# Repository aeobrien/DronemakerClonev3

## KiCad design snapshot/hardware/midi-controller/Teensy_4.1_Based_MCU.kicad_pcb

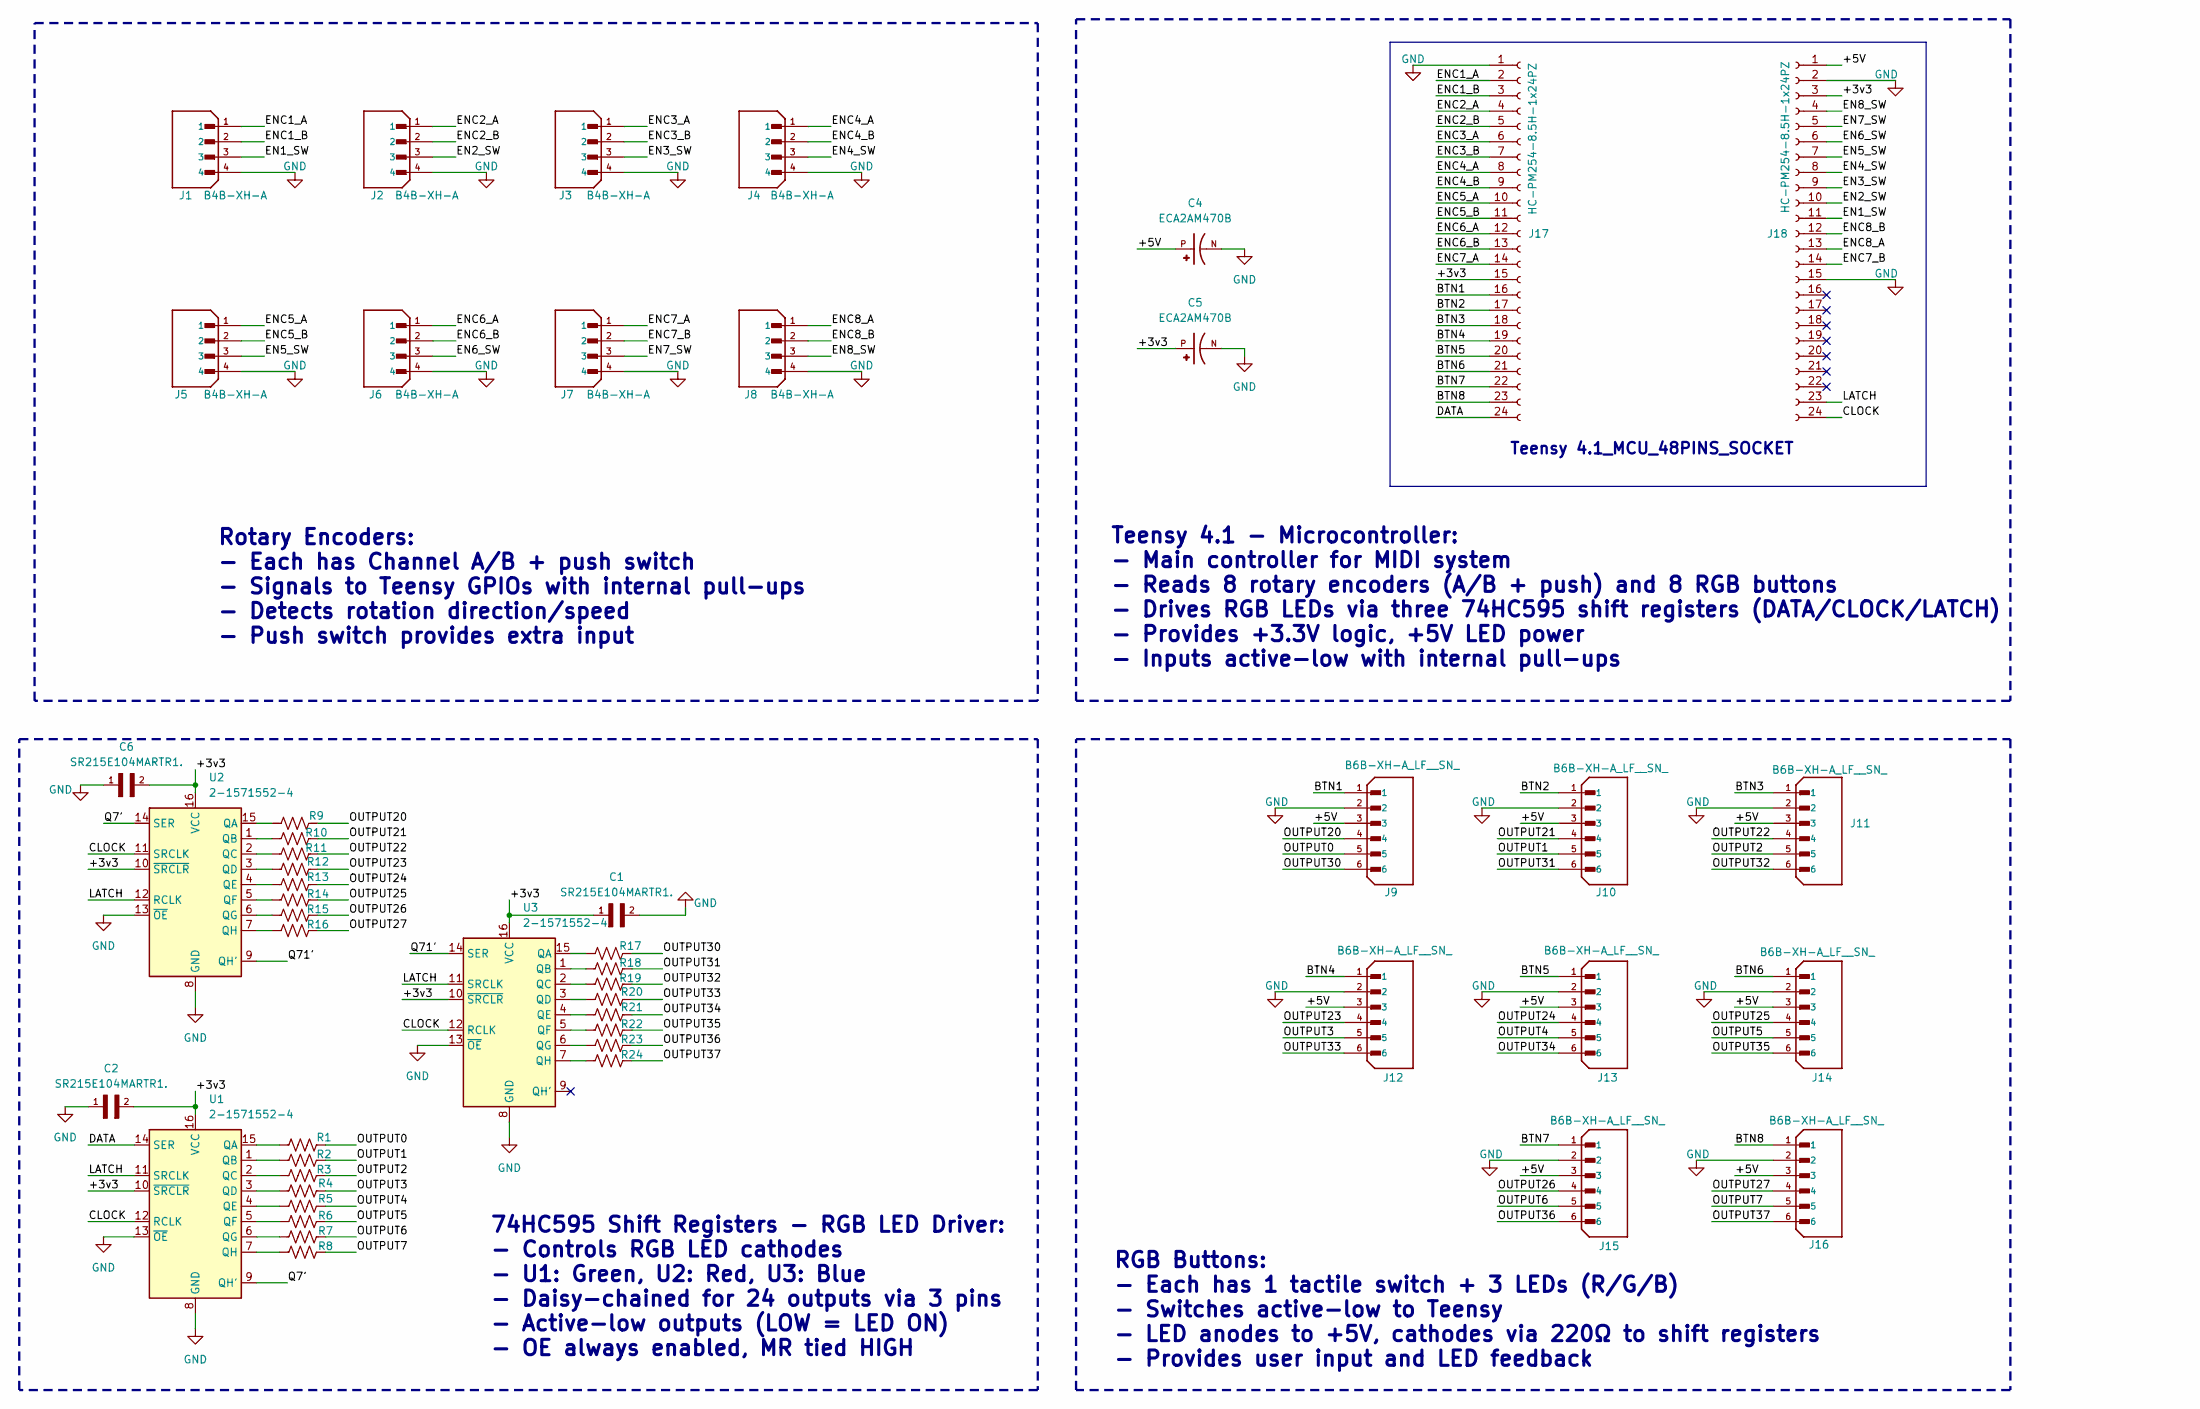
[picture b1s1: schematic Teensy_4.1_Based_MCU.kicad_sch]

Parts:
C1, C2, C6: SR215E104MARTR1.; CAPRR508W50L508T317H508; PARTREV 081816
C4, C5: ECA2AM470B; CAPPRD500W60D1000H2000; PARTREV 20-DEC-19
J1, J2, J3, J4, J5, J6, J7, J8: B4B-XH-A; JST_B4B-XH-A; PARTREV 7/4/21
J9, J10, J11, J12, J13, J14, J15, J16: B6B-XH-A_LF__SN_; JST_B6B-XH-A; PARTREV 7/4/21
J17, J18: HC-PM254-8.5H-1x24PZ; PinSocket_1x24_P2.54mm_Vertical
R1, R2, R3, R4, R5, R6, R7, R8, R9, R10, R11, R12, R13, R14, R15, R16, R17, R18, R19, R20, R21, R22, R23, R24: 220R; R_Axial_DIN0207_L6.3mm_D2.5mm_P10.16mm_Horizontal
U1, U2, U3: 2-1571552-4; DIP-16_W7.62mm_Socket

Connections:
/+3v3: C1.1, C2.2, C5.P, C6.2, J17.15, J18.3, U1.10 (~SRCLR), U1.16 (VCC), U2.10 (~SRCLR), U2.16 (VCC), U3.10 (~SRCLR), U3.16 (VCC)
/+5V: C4.P, J9.3, J10.3, J11.3, J12.3, J13.3, J14.3, J15.3, J16.3, J18.1
/BTN1: J9.1, J17.16
/BTN2: J10.1, J17.17
/BTN3: J11.1, J17.18
/BTN4: J12.1, J17.19
/BTN5: J13.1, J17.20
/BTN6: J14.1, J17.21
/BTN7: J15.1, J17.22
/BTN8: J16.1, J17.23
/CLOCK: J18.24, U1.12 (RCLK), U2.11 (SRCLK), U3.12 (RCLK)
/DATA: J17.24, U1.14 (SER)
/EN1_SW: J1.3, J18.11
/EN2_SW: J2.3, J18.10
/EN3_SW: J3.3, J18.9
/EN4_SW: J4.3, J18.8
/EN5_SW: J5.3, J18.7
/EN6_SW: J6.3, J18.6
/EN7_SW: J7.3, J18.5
/EN8_SW: J8.3, J18.4
/ENC1_A: J1.1, J17.2
/ENC1_B: J1.2, J17.3
/ENC2_A: J2.1, J17.4
/ENC2_B: J2.2, J17.5
/ENC3_A: J3.1, J17.6
/ENC3_B: J3.2, J17.7
/ENC4_A: J4.1, J17.8
/ENC4_B: J4.2, J17.9
/ENC5_A: J5.1, J17.10
/ENC5_B: J5.2, J17.11
/ENC6_A: J6.1, J17.12
/ENC6_B: J6.2, J17.13
/ENC7_A: J7.1, J17.14
/ENC7_B: J7.2, J18.14
/ENC8_A: J8.1, J18.13
/ENC8_B: J8.2, J18.12
/LATCH: J18.23, U1.11 (SRCLK), U2.12 (RCLK), U3.11 (SRCLK)
/OUTPUT0: J9.5, R1.2
/OUTPUT1: J10.5, R2.2
/OUTPUT2: J11.5, R3.2
/OUTPUT3: J12.5, R4.2
/OUTPUT4: J13.5, R5.2
/OUTPUT5: J14.5, R6.2
/OUTPUT6: J15.5, R7.2
/OUTPUT7: J16.5, R8.2
/OUTPUT20: J9.4, R9.2
/OUTPUT21: J10.4, R10.2
/OUTPUT22: J11.4, R11.2
/OUTPUT23: J12.4, R12.2
/OUTPUT24: J13.4, R13.2
/OUTPUT25: J14.4, R14.2
/OUTPUT26: J15.4, R15.2
/OUTPUT27: J16.4, R16.2
/OUTPUT30: J9.6, R17.2
/OUTPUT31: J10.6, R18.2
/OUTPUT32: J11.6, R19.2
/OUTPUT33: J12.6, R20.2
/OUTPUT34: J13.6, R21.2
/OUTPUT35: J14.6, R22.2
/OUTPUT36: J15.6, R23.2
/OUTPUT37: J16.6, R24.2
/Q7': U1.9 (QH'), U2.14 (SER)
/Q71': U2.9 (QH'), U3.14 (SER)
GND: C1.2, C2.1, C4.N, C5.N, C6.1, J1.4, J2.4, J3.4, J4.4, J5.4, J6.4, J7.4, J8.4, J9.2, J10.2, J11.2, J12.2, J13.2, J14.2, J15.2, J16.2, J17.1, J18.2, J18.15, U1.8 (GND), U1.13 (~OE), U2.8 (GND), U2.13 (~OE), U3.8 (GND), U3.13 (~OE)
unnamed: R1.1, U1.15 (QA)
unnamed: R2.1, U1.1 (QB)
unnamed: R3.1, U1.2 (QC)
unnamed: R4.1, U1.3 (QD)
unnamed: R5.1, U1.4 (QE)
unnamed: R6.1, U1.5 (QF)
unnamed: R7.1, U1.6 (QG)
unnamed: R8.1, U1.7 (QH)
unnamed: R9.1, U2.15 (QA)
unnamed: R10.1, U2.1 (QB)
unnamed: R11.1, U2.2 (QC)
unnamed: R12.1, U2.3 (QD)
unnamed: R13.1, U2.4 (QE)
unnamed: R14.1, U2.5 (QF)
unnamed: R15.1, U2.6 (QG)
unnamed: R16.1, U2.7 (QH)
unnamed: R17.1, U3.15 (QA)
unnamed: R18.1, U3.1 (QB)
unnamed: R19.1, U3.2 (QC)
unnamed: R20.1, U3.3 (QD)
unnamed: R21.1, U3.4 (QE)
unnamed: R22.1, U3.5 (QF)
unnamed: R23.1, U3.6 (QG)
unnamed: R24.1, U3.7 (QH)

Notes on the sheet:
Rotary Encoders: - Each has Channel A/B + push switch - Signals to Teensy GPIOs with internal pull-ups - Detects rotation direction/speed - Push switch provides extra input
Teensy 4.1_MCU_48PINS_SOCKET
Teensy 4.1 - Microcontroller: - Main controller for MIDI system - Reads 8 rotary encoders (A/B + push) and 8 RGB buttons - Drives RGB LEDs via three 74HC595 shift registers (DATA/CLOCK/LATCH) - Provides +3.3V logic, +5V LED power - Inputs active-low with internal pull-ups
RGB Buttons: - Each has 1 tactile switch + 3 LEDs (R/G/B) - Switches active-low to Teensy - LED anodes to +5V, cathodes via 220Ω to shift registers - Provides user input and LED feedback
74HC595 Shift Registers - RGB LED Driver: - Controls RGB LED cathodes - U1: Green, U2: Red, U3: Blue - Daisy-chained for 24 outputs via 3 pins - Active-low outputs (LOW = LED ON) - OE always enabled, MR tied HIGH

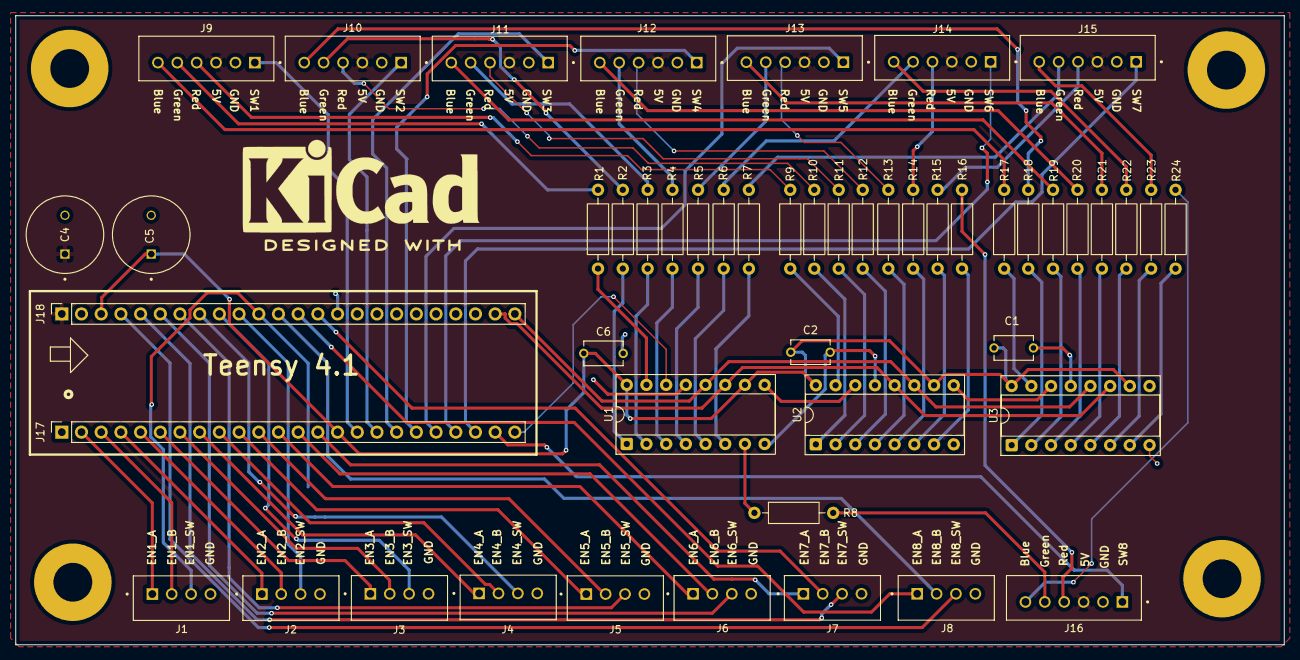
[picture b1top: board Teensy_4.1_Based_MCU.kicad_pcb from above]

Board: 2 copper layers, 163.6 x 81.1 mm, 50 parts (0 on the bottom side), 88 nets.

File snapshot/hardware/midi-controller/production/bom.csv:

Designator,Footprint,Quantity,Value,LCSC Part #
"C1, C2, C6",CAPRR508W50L508T317H508,3,SR215E104MARTR1.,
"C4, C5",CAPPRD500W60D1000H2000,2,ECA2AM470B,
"J1, J2, J3, J4, J5, J6, J7, J8",JST_B4B-XH-A,8,B4B-XH-A,
"J10, J11, J12, J13, J14, J15, J16, J9",JST_B6B-XH-A,8,B6B-XH-A_LF__SN_,
"J17, J18",PinSocket_1x24_P2.54mm_Vertical,2,HC-PM254-8.5H-1x24PZ,
"R1, R10, R11, R12, R13, R14, R15, R16, R17, R18, R19, R2, R20, R21, R22, R23, R24, R3, R4, R5, R6, R7, R8, R9",R_Axial_DIN0207_L6.3mm_D2.5mm_P10.16mm_Horizontal,24,220R,
"U1, U2, U3",DIP-16_W7.62mm_Socket,3,2-1571552-4,
